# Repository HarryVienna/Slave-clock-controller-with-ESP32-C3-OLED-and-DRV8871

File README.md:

# ESP32-C3 Slave Clock Controller

A compact, affordable, and robust controller for analog slave clocks and flip clocks (e.g., Bodet), based on the **ESP32-C3** microcontroller and the **DRV8871** H-Bridge driver.

## 📖 Overview

This project replaces bulky and expensive master clocks with a tiny PCB powered by a single Li-Ion battery. It synchronizes time via NTP and offers a web-based configuration interface.

**Key Features:**
* **Universal Support:** Works with standard 12V/24V slave clocks and Bodet flip clocks (including date motor support).
* **Compact Design:** Built around the tiny ESP32-C3 (RISC-V) and DRV8871.
* **Battery Backup:** Integrated TP4056 charging logic with deep discharge protection; keeps time during power outages.
* **WiFi Provisioning:** Easy setup via a Captive Portal (no hardcoded credentials).
* **OLED Display:** Shows status, IP, and current time (0.42" OLED).
* **Automatic Catch-up:** Automatically fast-forwards the clock if it lags behind system time.

🔗 **Read the full story and build log:** [Harald Kreuzer's Blog](https://www.haraldkreuzer.net/en/news/slave-clock-controller-esp32-c3-and-drv8871-compact-and-affordable)

## 🛠 Hardware Components

The system is built using four main modules:

1.  **Microcontroller:** ESP32-C3 (RISC-V, Single Core) with 0.42" OLED.
2.  **Motor Driver:** DRV8871 H-Bridge (3.6A peak, 6.5V-45V).
3.  **Power Management:** TP4056 USB-C Li-Ion charger.
4.  **Voltage Booster:** SX1308 Step-Up Converter (boosts battery voltage to 12V/24V).

> **Note for Bodet Clocks:** The PCB includes slots for specific diodes to drop the voltage for the 3V date motor found in Bodet flip clocks.

## 🔌 PCB

## 💻 Software Architecture

The firmware is written in C++ using the **ESP-IDF Framework**. It is modular and uses FreeRTOS tasks.

```mermaid
graph TD
    Main[main.cpp] --> SlaveClock
    Main --> Display
    Main --> Button
    Main --> WifiProv[WifiProvisioner]
    
    SlaveClock -->|GPIO| DRV8871[Motor Driver]
    Display -->|I2C| OLED[SSD1306]
    Button -->|GPIO| UserInput
    WifiProv -->|WiFi| SNTP[NTP Server]
```

### Modules
* **SlaveClock:** Manages the Lavet stepper motor logic (polarity inversion) and tracks the hands' position.
* **Display:** Handles the UI via `u8g2` library, including a screensaver to prevent burn-in.
* **Button:** Debounces input and detects Short Press, Long Press, and Double Click.
* **WifiProvisioner:** Handles the Captive Portal and SNTP synchronization.

## 🤝 Acknowledgments

* **PCBWay** for sponsoring the PCB manufacturing for this project.
* **u8g2** library for the display graphics.

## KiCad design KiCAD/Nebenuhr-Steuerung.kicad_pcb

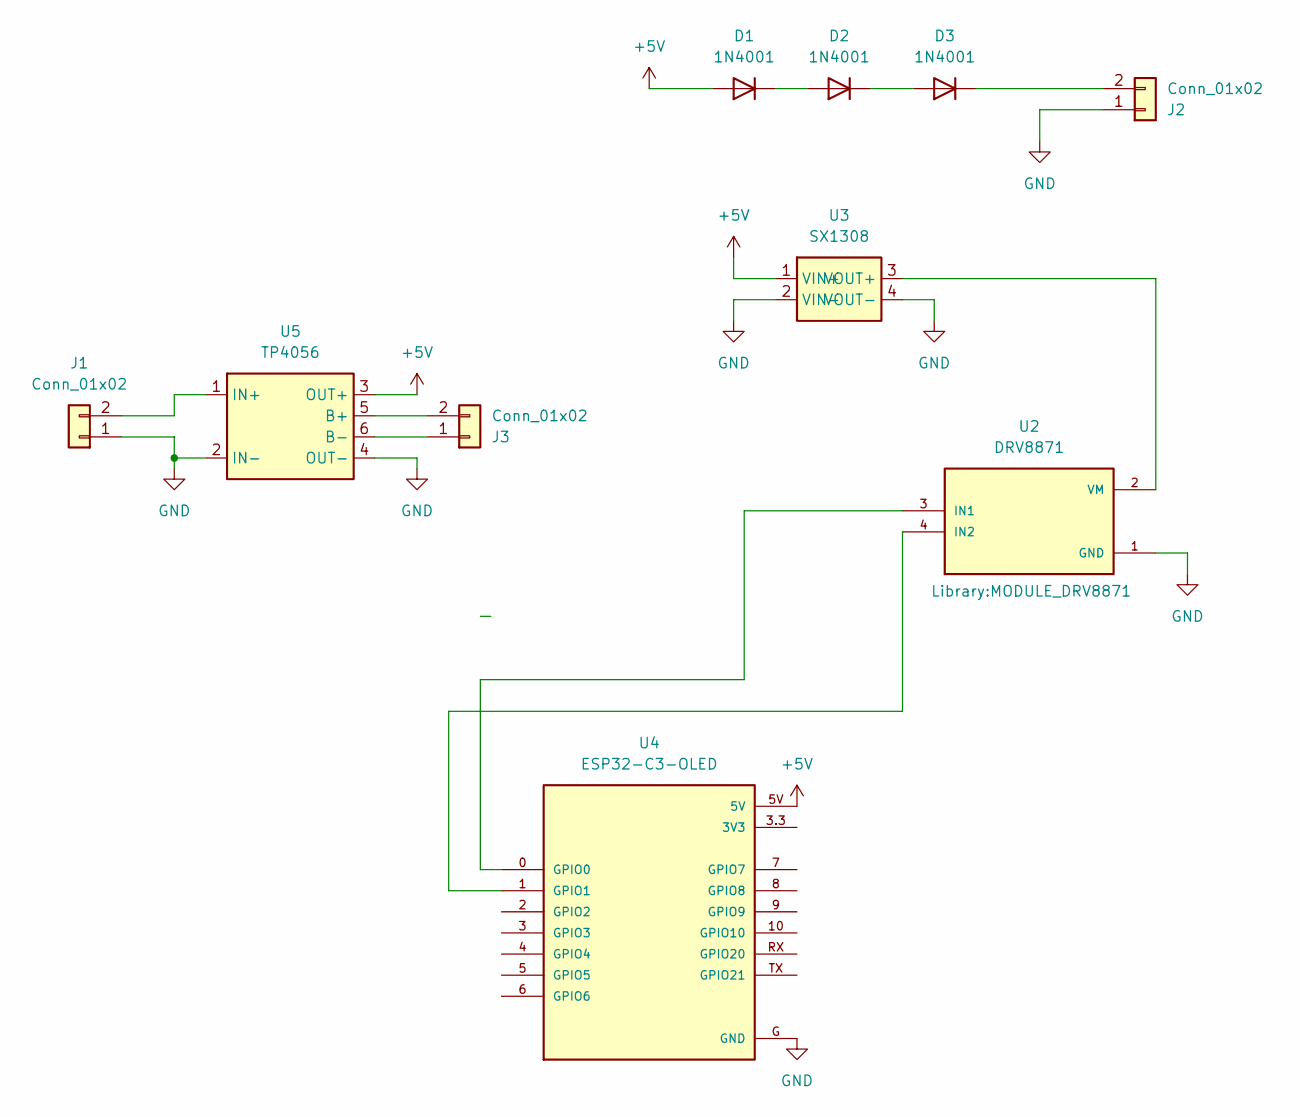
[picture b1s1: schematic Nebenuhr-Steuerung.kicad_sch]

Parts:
D1, D2, D3: 1N4001; D_DO-41_SOD81_P10.16mm_Horizontal
J1, J2, J3: Conn_01x02; TerminalBlock_Phoenix_PT-1,5-2-5.0-H_1x02_P5.00mm_Horizontal
U2: DRV8871; MODULE_DRV8871; PARTREV 2021-11-15
U3: SX1308; SX1308_Boost_Module
U4: ESP32-C3-OLED; MODULE_ESP32-C3_OLED
U5: TP4056; TP4056_Module_Protect

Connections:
+5V: D1.2 (A), U3.1 (VIN+), U4.5V, U5.3 (OUT+)
GND: J1.1, J2.1, U2.1 (GND), U3.2 (VIN-), U3.4 (VOUT-), U4.G (GND), U5.2 (IN-), U5.4 (OUT-)
unnamed: D1.1 (K), D2.2 (A)
unnamed: D2.1 (K), D3.2 (A)
unnamed: D3.1 (K), J2.2
unnamed: J1.2, U5.1 (IN+)
unnamed: J3.1, U5.6 (B-)
unnamed: J3.2, U5.5 (B+)
unnamed: U2.3 (IN1), U4.0 (GPIO0)
unnamed: U2.4 (IN2), U4.1 (GPIO1)
unnamed: U2.2 (VM), U3.3 (VOUT+)

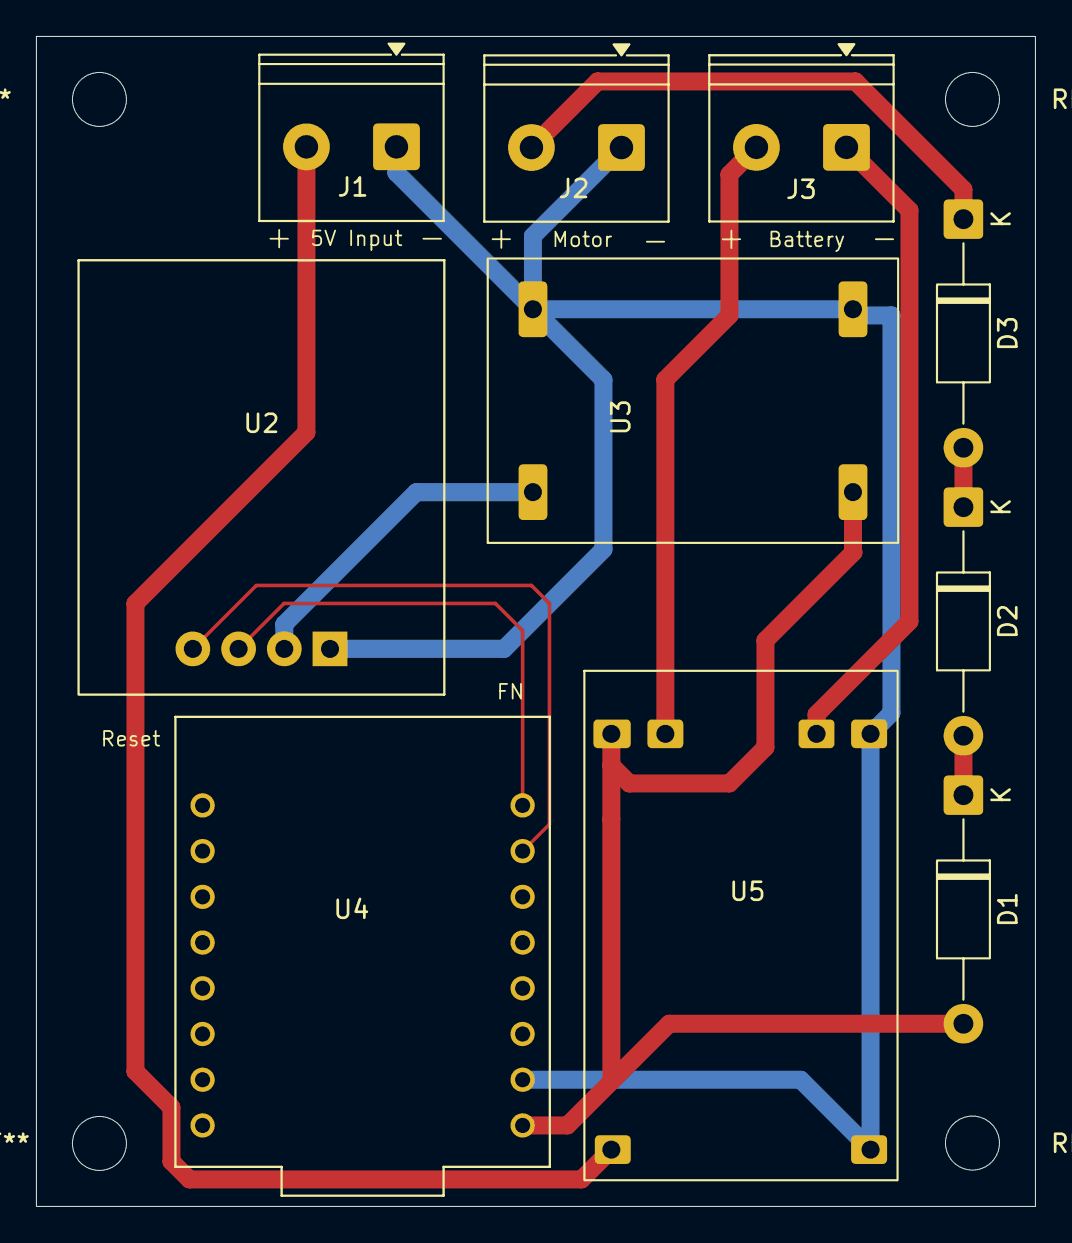
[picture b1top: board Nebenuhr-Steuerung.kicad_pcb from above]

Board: 2 copper layers, 55.5 x 65.0 mm, 10 parts (0 on the bottom side), 11 nets.

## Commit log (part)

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2026-01-22 Init
2026-01-22 Revise README for ESP32.C3 and DRV8871 driver
    Updated project description to reflect the use of ESP32.C3 and DRV8871 driver.
2026-01-31 Add Screensaver
2026-02-03 Revise README for ESP32-C3 Slave Clock Controller
    This README update provides a comprehensive overview of the ESP32-C3 Slave Clock Controller project
2026-02-14 Revise PCB section in README
    Updated section headings and removed redundant text about circuit design.
2026-03-07 Update WiFi provisioning
2026-06-15 Update EDP-IDF version
2026-06-15 Add KiCAD files

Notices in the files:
README.md:
License: MIT
